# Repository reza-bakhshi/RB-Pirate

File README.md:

<div align="center">

# RB-Pirate

**An RP2350B multi-protocol hardware exploration and debugging tool**

</div>

RB-Pirate is an RP2350B-based tool for communicating with and debugging electronic devices. It combines eight buffered I/O pins, programmable target power, voltage and current monitoring, logic capture, and microSD storage. The terminal interface supports serial-bus interaction and hardware automation.

## Start here

This repository contains the KiCad hardware design. Open [RB-Pirate.kicad_pro](RB-Pirate.kicad_pro) to inspect the schematic and PCB together.

| Resource | Contents |
|---|---|
| [RB-Pirate.kicad_sch](RB-Pirate.kicad_sch) | Schematic entry point |
| [RB-Pirate.kicad_pcb](RB-Pirate.kicad_pcb) | PCB layout |
| [img](img) | Board renders |
| [Custom firmware](https://github.com/reza-bakhshi/RB-Pirate-Firmware) | Build, flashing, terminal operation, and protocol guides |
| [Host automation](https://github.com/reza-bakhshi/RB-Pirate-Skill) | Python serial runner and agent reference material |

Firmware determines which protocol modes and tools are available. RF, infrared, and NFC workflows require the corresponding external hardware; those modules are not built into the base board.

## PCB gallery

<table>
  <tr>
    <th width="50%">Top</th>
    <th width="50%">Bottom</th>
  </tr>
  <tr>
    <td></td>
    <td></td>
  </tr>
</table>

## Hardware features

### RP2350B platform

- Raspberry Pi RP2350B microcontroller
- 128 Mbit program flash
- Dual-core processing and flexible PIO peripherals
- USB-C host connection
- Built-in USB bootloader for straightforward firmware updates
- SWD header, BOOTSEL button, and RESET button
- Two-layer, 1.6 mm PCB designed with KiCad 10

### Eight buffered I/O pins

- 1.65 V to 5 V operating range
- Three-state outputs
- Voltage measurement on every I/O pin
- Individually controllable 10 kΩ pull-up resistors
- Standard 10-pin, 2.54 mm header with GND, BPIO7–BPIO0, and VOUT

### Programmable target power supply

- Programmable 1 V to 5 V output
- Programmable 0 mA to 500 mA current limit
- Real-time current sensing
- Resettable digital fuse
- Output protection circuitry

### Removable microSD storage

- Stores global and protocol-mode settings
- Provides space for logs, captures, dumps, and scripts
- Accessible through the firmware's USB storage interface
- Removable and easy to replace or upgrade

## Software features

### Terminal and logic analysis

- Color VT100 terminal interface
- Live status toolbar with voltage and current monitoring
- Follow-Along Logic Analyzer capture while commands are executed
- Live bus-activity inspection and analysis workflows

### Protocols and workflows

- I²C, SPI, UART, half-duplex UART, 1-Wire, 2-Wire, and 3-Wire communication
- Digital I/O and serial LED control
- JTAG and SWD discovery
- Logic capture and protocol analysis
- EEPROM, flash, FRAM, sensor, and smart-card interaction
- Firmware programming, memory access, scripting, and automation workflows

## Firmware

> [!IMPORTANT]
> ### Use the custom RB-Pirate firmware
>
> Install firmware only from the
> **[RB-Pirate Firmware repository](https://github.com/reza-bakhshi/RB-Pirate-Firmware)**.
> Do not use the mainline Bus Pirate firmware on this board. The custom firmware
> provides the correct hardware configuration, microSD support, and optional
> RGB & Button HAT integration for RB-Pirate.

Build instructions, firmware releases, installation steps, and update
instructions are maintained in the custom firmware repository.

## Optional RGB & Button HAT

The **[RB-Pirate RGB & Button HAT](https://github.com/reza-bakhshi/RB-Pirate-RGB-HAT)**
adds RGB visual feedback and a programmable user button.

The optional HAT provides:

- RGB status indication and animations
- Introduction and party-mode effects
- A button for escaping from active modes
- Scriptable user input for automation and custom workflows

RB-Pirate operates normally without the HAT. Add it only when RGB feedback or
physical button input is useful for your setup.

## License

RB-Pirate is released under the [MIT License](LICENSE).

Third-party components and libraries remain subject to their respective
licenses.

---

<div align="center">
  <sub>Built for hardware exploration, debugging, and experimentation.</sub>
</div>

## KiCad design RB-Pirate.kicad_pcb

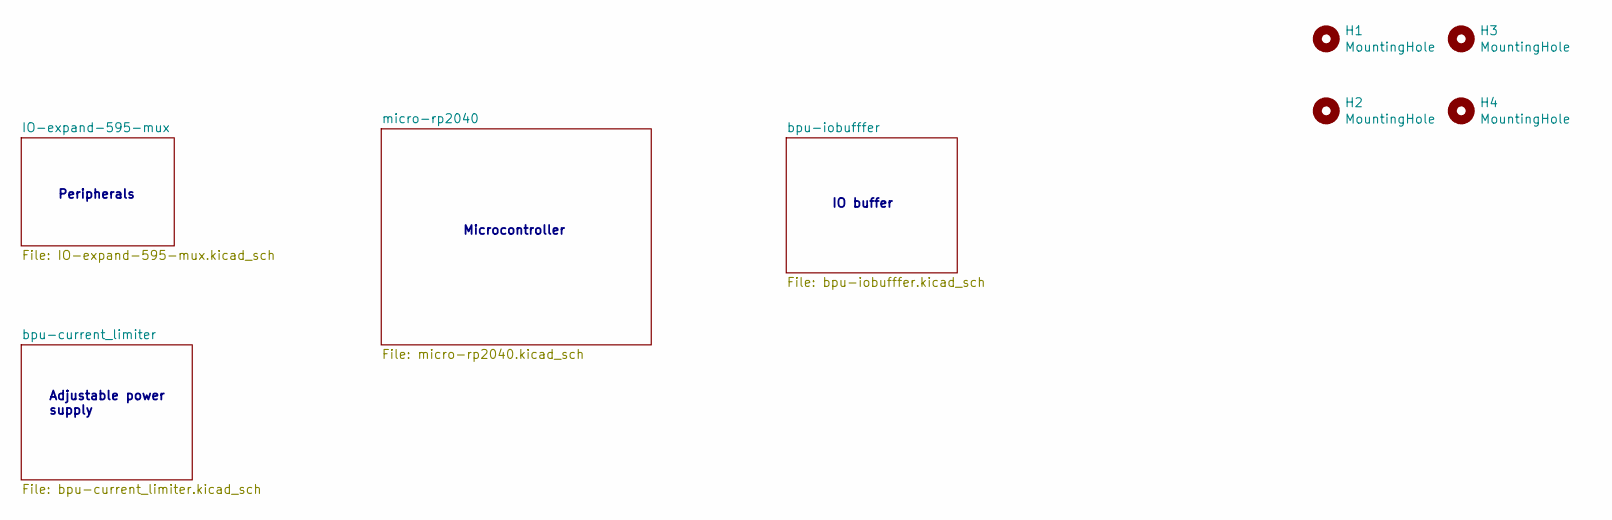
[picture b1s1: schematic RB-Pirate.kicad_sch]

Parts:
H1, H2, H3, H4: MountingHole; MountingHole_3.2mm_M3

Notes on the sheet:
Microcontroller
Adjustable power supply
IO buffer
Peripherals

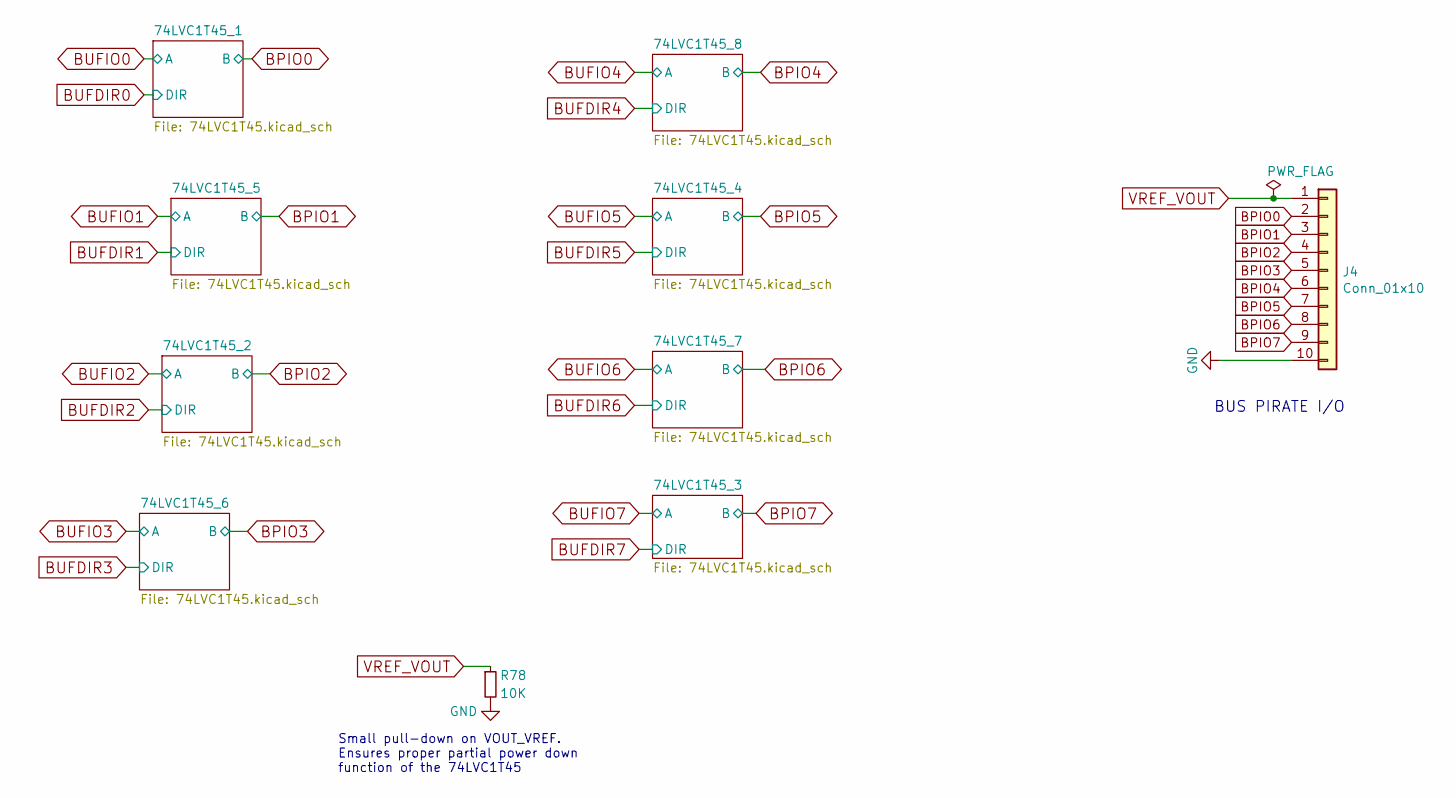
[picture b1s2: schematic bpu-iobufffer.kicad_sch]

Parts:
J4: Conn_01x10; PinHeader_1x10_P2.54mm_Horizontal
R78: 10K; R_0402_1005Metric

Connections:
BPIO0: J4.2; also elsewhere on the board
BPIO1: J4.3; also elsewhere on the board
BPIO2: J4.4; also elsewhere on the board
BPIO3: J4.5; also elsewhere on the board
BPIO4: J4.6; also elsewhere on the board
BPIO5: J4.7; also elsewhere on the board
BPIO6: J4.8; also elsewhere on the board
BPIO7: J4.9; also elsewhere on the board
GND: J4.10, R78.2; also elsewhere on the board
VREF_VOUT: J4.1, R78.1; also elsewhere on the board

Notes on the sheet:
Small pull-down on VOUT_VREF. Ensures proper partial power down function of the 74LVC1T45
BUS PIRATE I/O

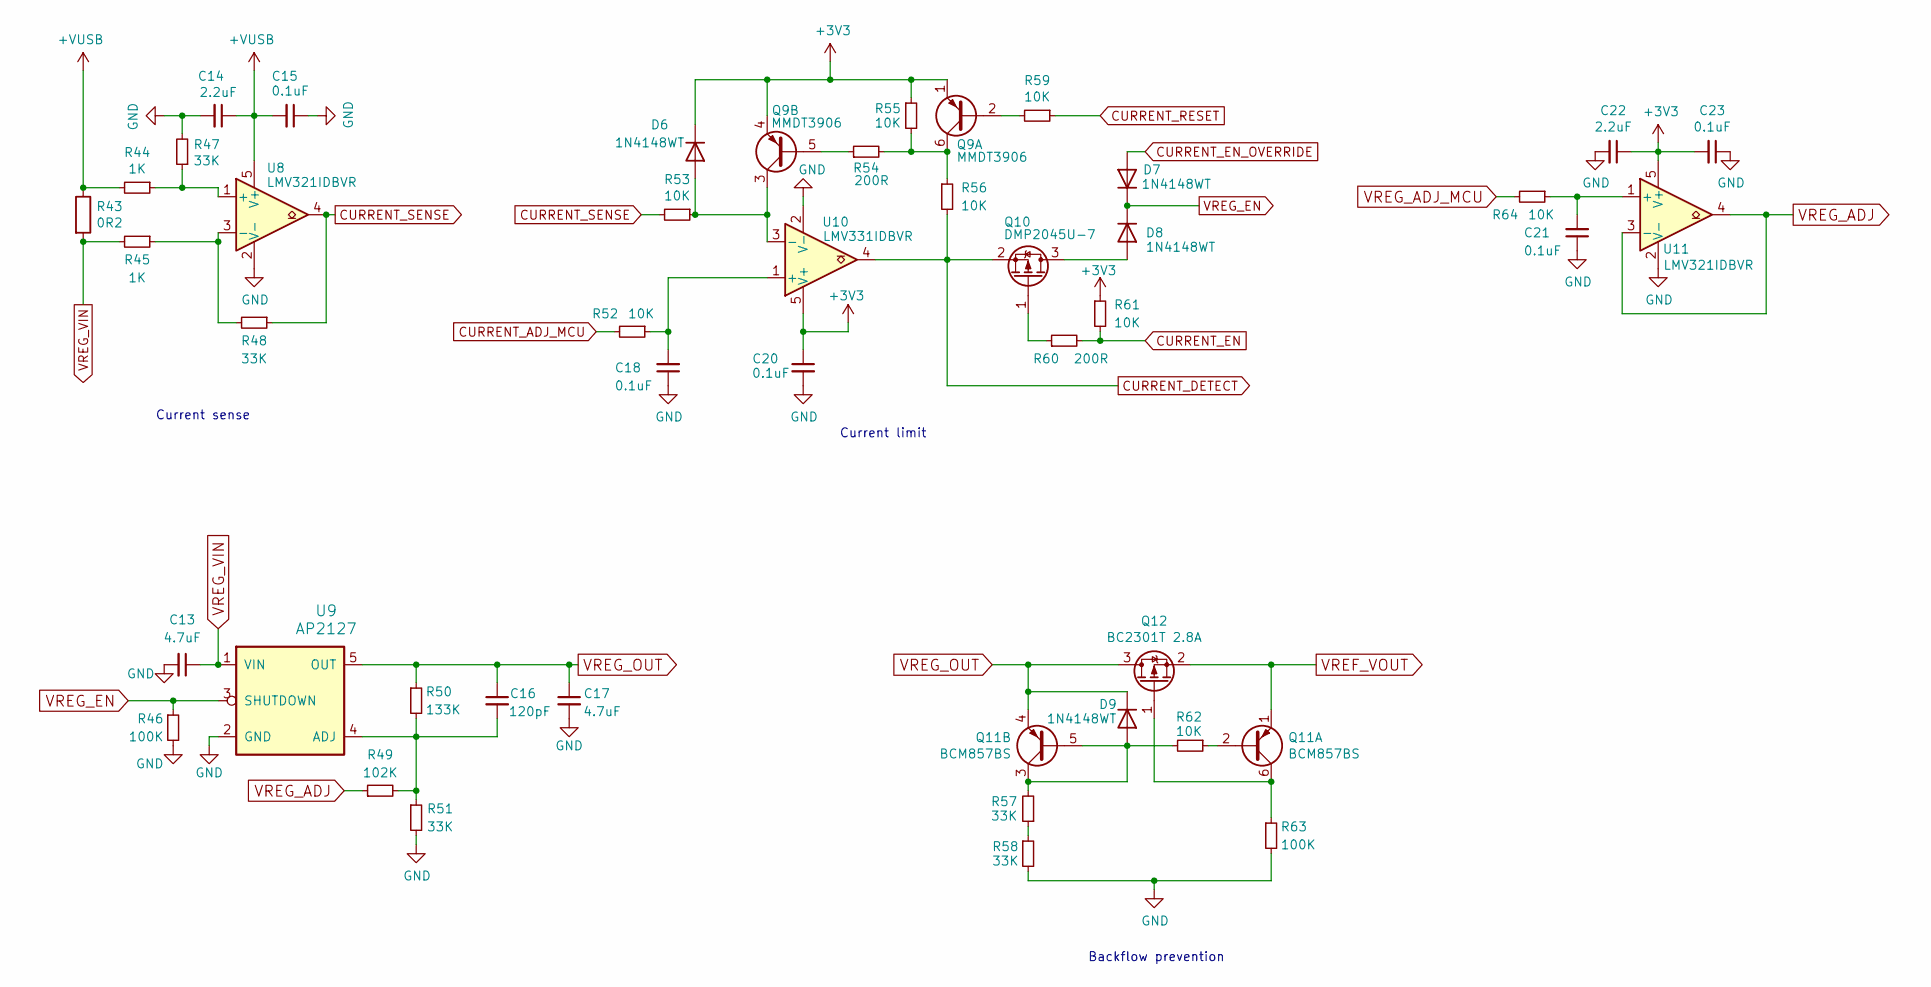
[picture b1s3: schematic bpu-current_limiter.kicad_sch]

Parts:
C13, C17: 4.7uF; C_0402_1005Metric
C14, C22: 2.2uF; C_0402_1005Metric
C15, C18, C20, C21, C23: 0.1uF; C_0402_1005Metric
C16: 120pF; C_0402_1005Metric
D6, D7, D8, D9: 1N4148WT; D_SOD-523
Q9: MMDT3906; SOT-363_SC-70-6
Q10: DMP2045U-7; SOT-23
Q11: BCM857BS; SOT-363_SC-70-6
Q12: BC2301T 2.8A; SOT-23
R43: 0R2; R_2512_6332Metric_Pad1.40x3.35mm_HandSolder
R44, R45: 1K; R_0402_1005Metric
R46, R63: 100K; R_0402_1005Metric
R47, R48, R51, R57, R58: 33K; R_0402_1005Metric
R49: 102K; R_0402_1005Metric
R50: 133K; R_0402_1005Metric
R52, R53, R55, R56, R59, R61, R62, R64: 10K; R_0402_1005Metric
R54, R60: 200R; R_0402_1005Metric
U8, U11: LMV321IDBVR; SOT-23-5
U9: AP2127; SOT-23-5
U10: LMV331IDBVR; SOT-23-5

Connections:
+3V3: C20.1, C22.1, C23.2, D6.1 (K), Q9.1 (E1), Q9.4 (E2), R55.1, R61.1, U10.5 (V+), U11.5 (V+); also elsewhere on the board
+VUSB: C14.1, C15.2, R43.1, R44.2, U8.5 (V+); also elsewhere on the board
CURRENT_ADJ_MCU: R52.2; also elsewhere on the board
CURRENT_DETECT: Q10.2 (S), R56.2, U10.4; also elsewhere on the board
CURRENT_EN: R60.2, R61.2; also elsewhere on the board
CURRENT_EN_OVERRIDE: D7.2 (A); also elsewhere on the board
CURRENT_RESET: R59.1; also elsewhere on the board
CURRENT_SENSE: R48.1, R53.2, U8.4; also elsewhere on the board
GND: C13.2, C14.2, C15.1, C17.2, C18.1, C20.2, C21.1, C22.2, C23.1, R46.2, R47.2, R51.2, R58.2, R63.2, U8.2 (V-), U9.2 (GND), U10.2 (V-), U11.2 (V-); also elsewhere on the board
unnamed: D6.2 (A), Q9.3 (C2), R53.1, U10.3 (-)
unnamed: D8.2 (A), Q10.3 (D)
unnamed: D9.2 (A), Q11.3 (C2), Q11.5 (B2), R57.2, R62.2
unnamed: Q9.2 (B1), R59.2
unnamed: Q9.6 (C1), R54.2, R55.2, R56.1
unnamed: Q9.5 (B2), R54.1
unnamed: Q10.1 (G), R60.1
unnamed: Q11.2 (B1), R62.1
unnamed: Q11.6 (C1), Q12.1 (G), R63.1
unnamed: R57.1, R58.1
unnamed: R44.1, R47.1, U8.1 (+)
unnamed: R45.1, R48.2, U8.3 (-)
unnamed: C16.2, R49.2, R50.2, R51.1, U9.4 (ADJ)
unnamed: C18.2, R52.1, U10.1 (+)
unnamed: C21.2, R64.1, U11.1 (+)
VREF_VOUT: Q11.1 (E1), Q12.2 (S); also elsewhere on the board
VREG_ADJ: R49.1, U11.3 (-), U11.4
VREG_ADJ_MCU: R64.2; also elsewhere on the board
VREG_EN: D7.1 (K), D8.1 (K), R46.1, U9.3 (SHUTDOWN)
VREG_OUT: C16.1, C17.1, D9.1 (K), Q11.4 (E2), Q12.3 (D), R50.1, U9.5 (OUT); also elsewhere on the board
VREG_VIN: C13.1, R43.2, R45.2, U9.1 (VIN)

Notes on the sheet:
Current sense
Backflow prevention
Current limit

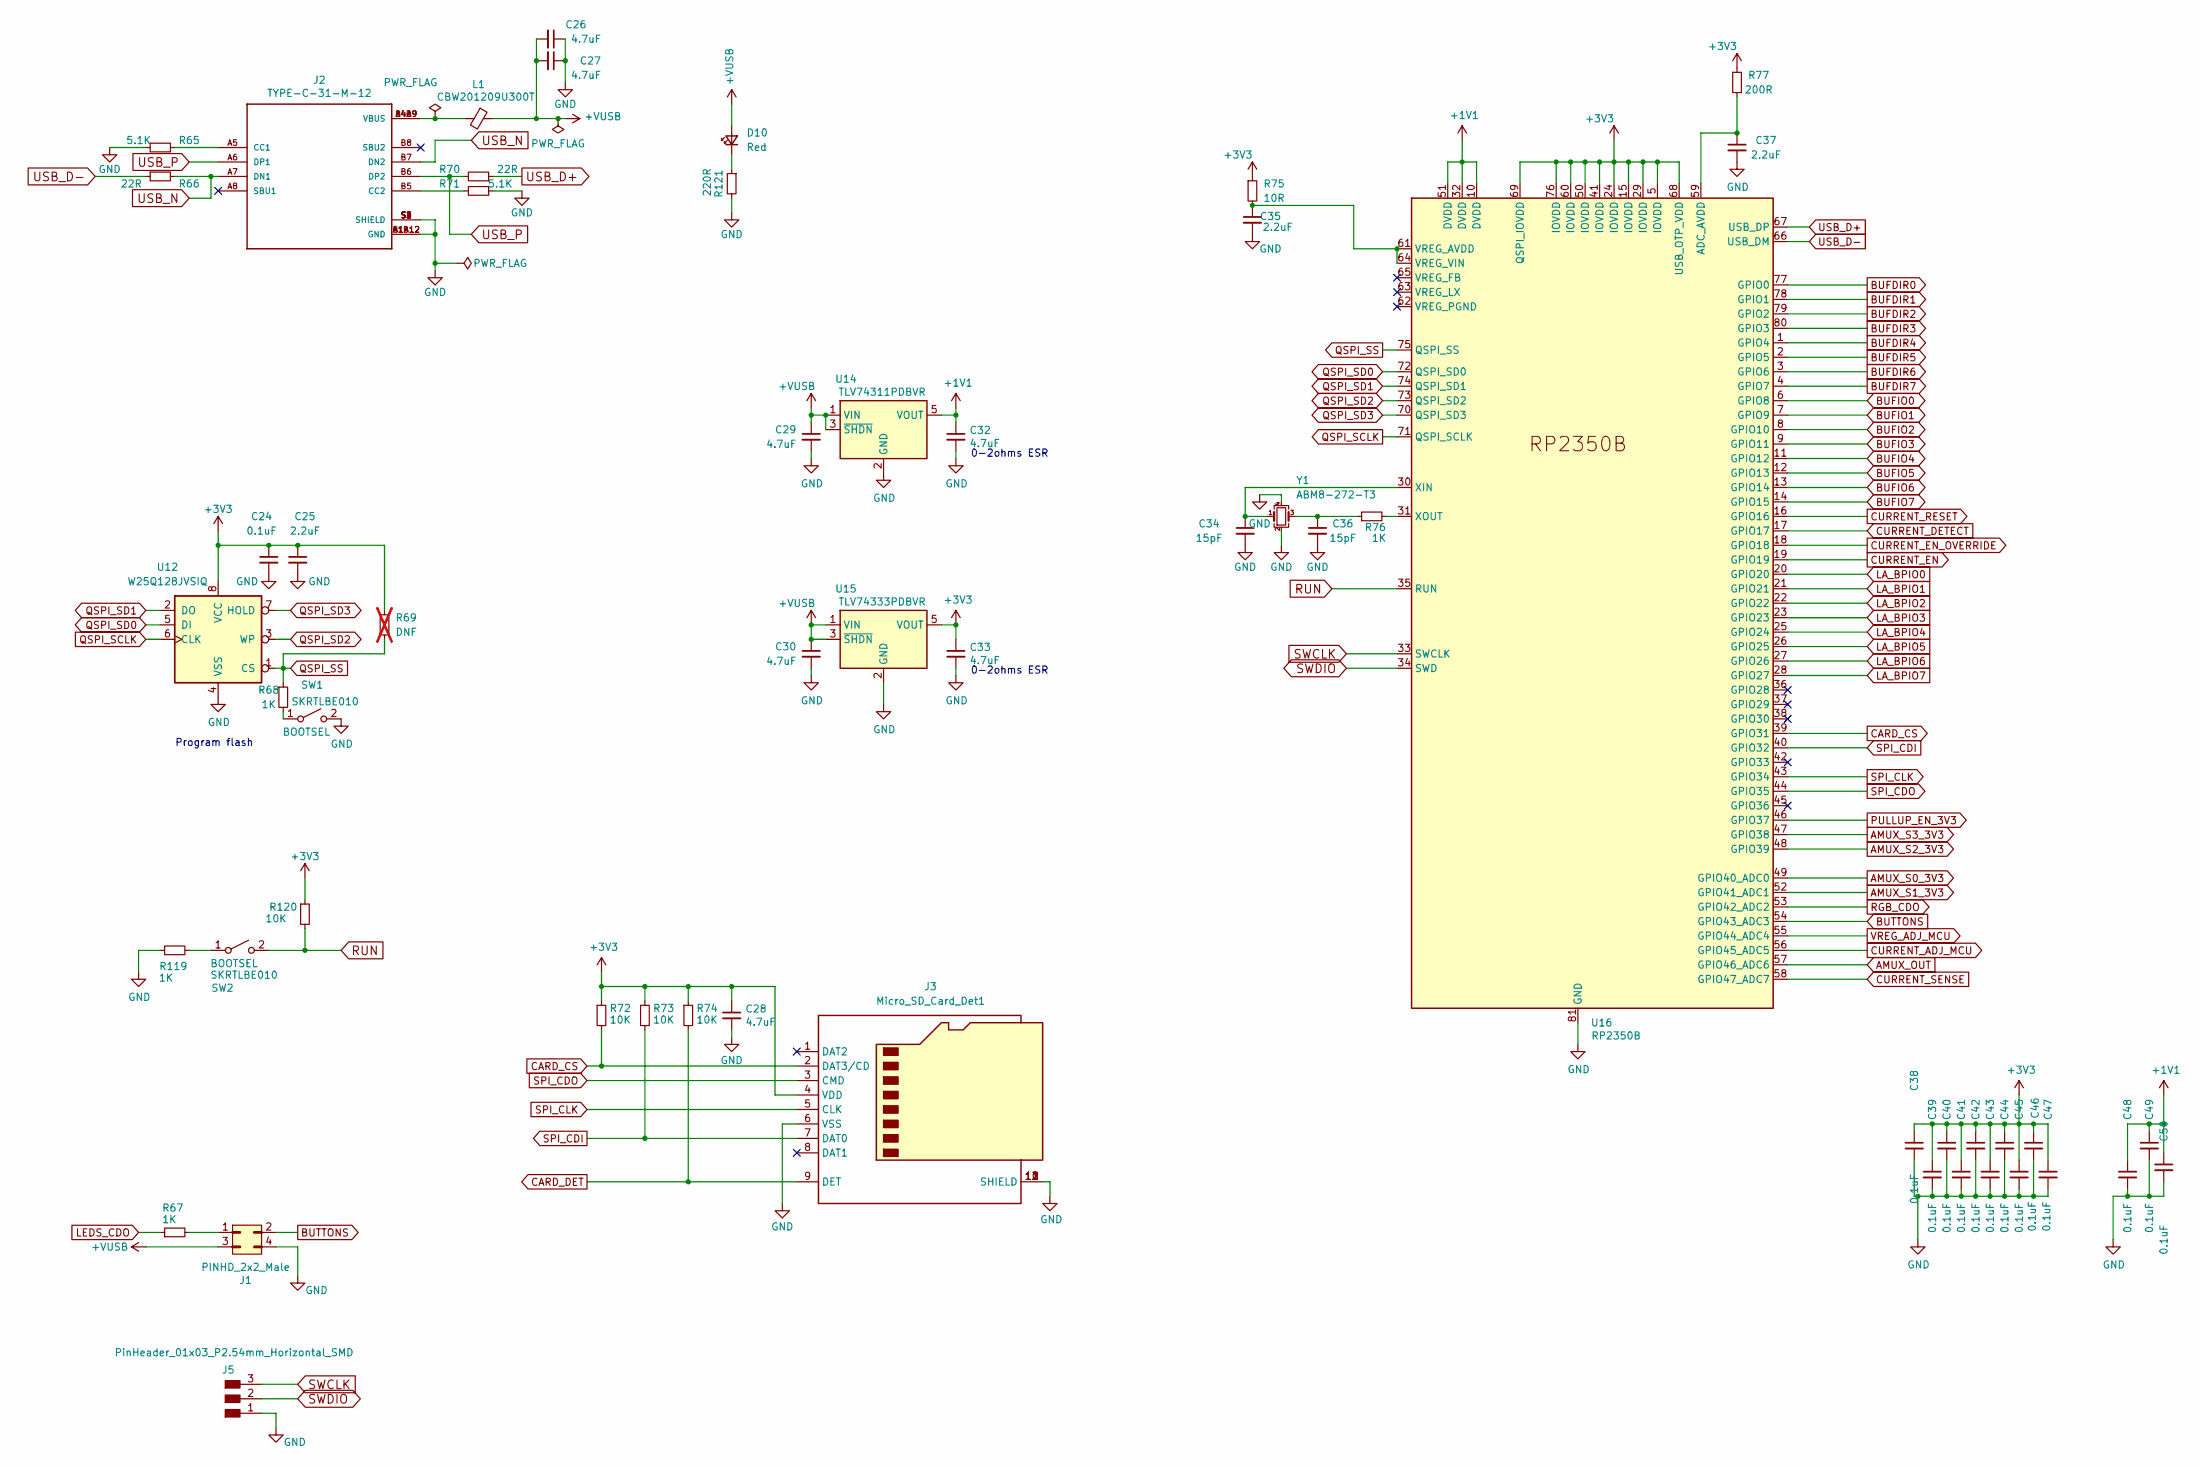
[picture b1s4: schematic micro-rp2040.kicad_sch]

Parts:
C24, C38, C39, C40, C41, C42, C43, C44, C45, C46, C47, C48, C49, C50: 0.1uF; C_0402_1005Metric
C25, C35, C37: 2.2uF; C_0402_1005Metric
C26, C27, C28, C29, C30, C32, C33: 4.7uF; C_0402_1005Metric
C34, C36: 15pF; C_0402_1005Metric
D10: Red; LED_0402_1005Metric_Red
J1: PINHD_2x2_Male; PinHeader_2x02_P2.54mm_Vertical_SMD
J2: TYPE-C-31-M-12; HRO_TYPE-C-31-M-12
J3: Micro_SD_Card_Det1; microSD_External_Pin
J5: PinHeader_01x03_P2.54mm_Horizontal_SMD
L1: CBW201209U300T; L_0805_2012Metric
R65, R71: 5.1K; R_0402_1005Metric
R66, R70: 22R; R_0402_1005Metric
R67, R68, R76, R119: 1K; R_0402_1005Metric
R69: DNF; R_0402_1005Metric; not fitted
R72, R73, R74, R120: 10K; R_0402_1005Metric
R75: 10R; R_0402_1005Metric
R77: 200R; R_0402_1005Metric
R121: 220R; R_0402_1005Metric
SW1, SW2: SKRTLBE010; Push_SMD_RA_4.5x3.4mm
U12: W25Q128JVSIQ; SOP-8_5.28x5.23mm_P1.27mm
U14: TLV74311PDBVR; SOT-23-5
U15: TLV74333PDBVR; SOT-23-5
U16: RP2350B; qfn80
Y1: ABM8-272-T3; Crystal_SMD_4Pin

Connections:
+1V1: C32.1, C48.1, C49.1, C50.1, U14.5 (VOUT), U16.10 (DVDD), U16.32 (DVDD), U16.51 (DVDD)
+3V3: C24.1, C25.1, C28.1, C33.1, C38.1, C39.1, C40.1, C41.1, C42.1, C43.1, C44.1, C45.1, C46.1, C47.1, J3.4 (VDD), R69.1, R72.1, R73.1, R74.1, R75.1, R77.1, R120.1, U12.8 (VCC), U15.5 (VOUT), U16.5 (IOVDD), U16.15 (IOVDD), U16.24 (IOVDD), U16.29 (IOVDD), U16.41 (IOVDD), U16.50 (IOVDD), U16.60 (IOVDD), U16.68 (USB_OTP_VDD), U16.69 (QSPI_IOVDD), U16.76 (IOVDD); also elsewhere on the board
+VUSB: C26.2, C27.2, C29.1, C30.1, D10.2 (A), J1.3, L1.1, U14.1 (VIN), U14.3 (~SHDN), U15.1 (VIN), U15.3 (~SHDN); also elsewhere on the board
AMUX_OUT: U16.57 (GPIO46_ADC6); also elsewhere on the board
AMUX_S0_3V3: U16.49 (GPIO40_ADC0); also elsewhere on the board
AMUX_S1_3V3: U16.52 (GPIO41_ADC1); also elsewhere on the board
AMUX_S2_3V3: U16.48 (GPIO39); also elsewhere on the board
AMUX_S3_3V3: U16.47 (GPIO38); also elsewhere on the board
BUFDIR0: U16.77 (GPIO0); also elsewhere on the board
BUFDIR1: U16.78 (GPIO1); also elsewhere on the board
BUFDIR2: U16.79 (GPIO2); also elsewhere on the board
BUFDIR3: U16.80 (GPIO3); also elsewhere on the board
BUFDIR4: U16.1 (GPIO4); also elsewhere on the board
BUFDIR5: U16.2 (GPIO5); also elsewhere on the board
BUFDIR6: U16.3 (GPIO6); also elsewhere on the board
BUFDIR7: U16.4 (GPIO7); also elsewhere on the board
BUFIO0: U16.6 (GPIO8); also elsewhere on the board
BUFIO1: U16.7 (GPIO9); also elsewhere on the board
BUFIO2: U16.8 (GPIO10); also elsewhere on the board
BUFIO3: U16.9 (GPIO11); also elsewhere on the board
BUFIO4: U16.11 (GPIO12); also elsewhere on the board
BUFIO5: U16.12 (GPIO13); also elsewhere on the board
BUFIO6: U16.13 (GPIO14); also elsewhere on the board
BUFIO7: U16.14 (GPIO15); also elsewhere on the board
BUTTONS: J1.2, U16.54 (GPIO43_ADC3)
CARD_CS: J3.2 (DAT3/CD), R72.2, U16.39 (GPIO31)
CARD_DET: J3.9 (DET), R74.2; also elsewhere on the board
CURRENT_ADJ_MCU: U16.56 (GPIO45_ADC5); also elsewhere on the board
CURRENT_DETECT: U16.17 (GPIO17); also elsewhere on the board
CURRENT_EN: U16.19 (GPIO19); also elsewhere on the board
CURRENT_EN_OVERRIDE: U16.18 (GPIO18); also elsewhere on the board
CURRENT_RESET: U16.16 (GPIO16); also elsewhere on the board
CURRENT_SENSE: U16.58 (GPIO47_ADC7); also elsewhere on the board
GND: C24.2, C25.2, C26.1, C27.1, C28.2, C29.2, C30.2, C32.2, C33.2, C34.2, C35.2, C36.2, C37.2, C38.2, C39.2, C40.2, C41.2, C42.2, C43.2, C44.2, C45.2, C46.2, C47.2, C48.2, C49.2, C50.2, J1.4, J2.A1B12 (GND), J2.B1A12 (GND), J2.S1 (SHIELD), J2.S2 (SHIELD), J2.S3 (SHIELD), J2.S4 (SHIELD), J3.6 (VSS), J3.10 (SHIELD), J3.11 (SHIELD), J3.12 (SHIELD), J3.13 (SHIELD), J5.1, R65.1, R71.1, R119.1, R121.2, SW1.2 (B), U12.4 (VSS), U14.2 (GND), U14.4 (GND), U15.2 (GND), U15.4 (GND), U16.81 (GND), Y1.2, Y1.4; also elsewhere on the board
LA_BPIO0: U16.20 (GPIO20); also elsewhere on the board
LA_BPIO1: U16.21 (GPIO21); also elsewhere on the board
LA_BPIO2: U16.22 (GPIO22); also elsewhere on the board
LA_BPIO3: U16.23 (GPIO23); also elsewhere on the board
LA_BPIO4: U16.25 (GPIO24); also elsewhere on the board
LA_BPIO5: U16.26 (GPIO25); also elsewhere on the board
LA_BPIO6: U16.27 (GPIO26); also elsewhere on the board
LA_BPIO7: U16.28 (GPIO27); also elsewhere on the board
LEDS_CDO: R67.1; also elsewhere on the board
unnamed: C36.1, R76.1, Y1.3
unnamed: D10.1 (K), R121.1
unnamed: J1.1, R67.2
unnamed: J2.A5 (CC1), R65.2
unnamed: J2.B5 (CC2), R71.2
unnamed: J2.A4B9 (VBUS), J2.B4A9 (VBUS), L1.2
unnamed: R68.2, SW1.1 (A)
unnamed: R119.2, SW2.1 (A)
unnamed: C37.1, R77.2, U16.59 (ADC_AVDD)
unnamed: C35.1, R75.2, U16.61 (VREG_AVDD), U16.64 (VREG_VIN)
unnamed: C34.1, U16.30 (XIN), Y1.1
unnamed: R76.2, U16.31 (XOUT)
PULLUP_EN_3V3: U16.46 (GPIO37); also elsewhere on the board
QSPI_SCLK: U12.6 (CLK), U16.71 (QSPI_SCLK)
QSPI_SD0: U12.5 (DI), U16.72 (QSPI_SD0)
QSPI_SD1: U12.2 (DO), U16.74 (QSPI_SD1)
QSPI_SD2: U12.3 (WP), U16.73 (QSPI_SD2)
QSPI_SD3: U12.7 (HOLD), U16.70 (QSPI_SD3)
QSPI_SS: R68.1, R69.2, U12.1 (CS), U16.75 (QSPI_SS)
RGB_CDO: U16.53 (GPIO42_ADC2); also elsewhere on the board
RUN: R120.2, SW2.2 (B), U16.35 (RUN)
SPI_CDI: J3.7 (DAT0), R73.2, U16.40 (GPIO32)
SPI_CDO: J3.3 (CMD), U16.44 (GPIO35)
SPI_CLK: J3.5 (CLK), U16.43 (GPIO34)
SWCLK: J5.3, U16.33 (SWCLK)
SWDIO: J5.2, U16.34 (SWD)
USB_D+: R70.1, U16.67 (USB_DP)
USB_D-: R66.1, U16.66 (USB_DM)
USB_N: J2.A7 (DN1), J2.B7 (DN2), R66.2
USB_P: J2.A6 (DP1), J2.B6 (DP2), R70.2
VREG_ADJ_MCU: U16.55 (GPIO44_ADC4); also elsewhere on the board

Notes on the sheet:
Program flash
0-2ohms ESR

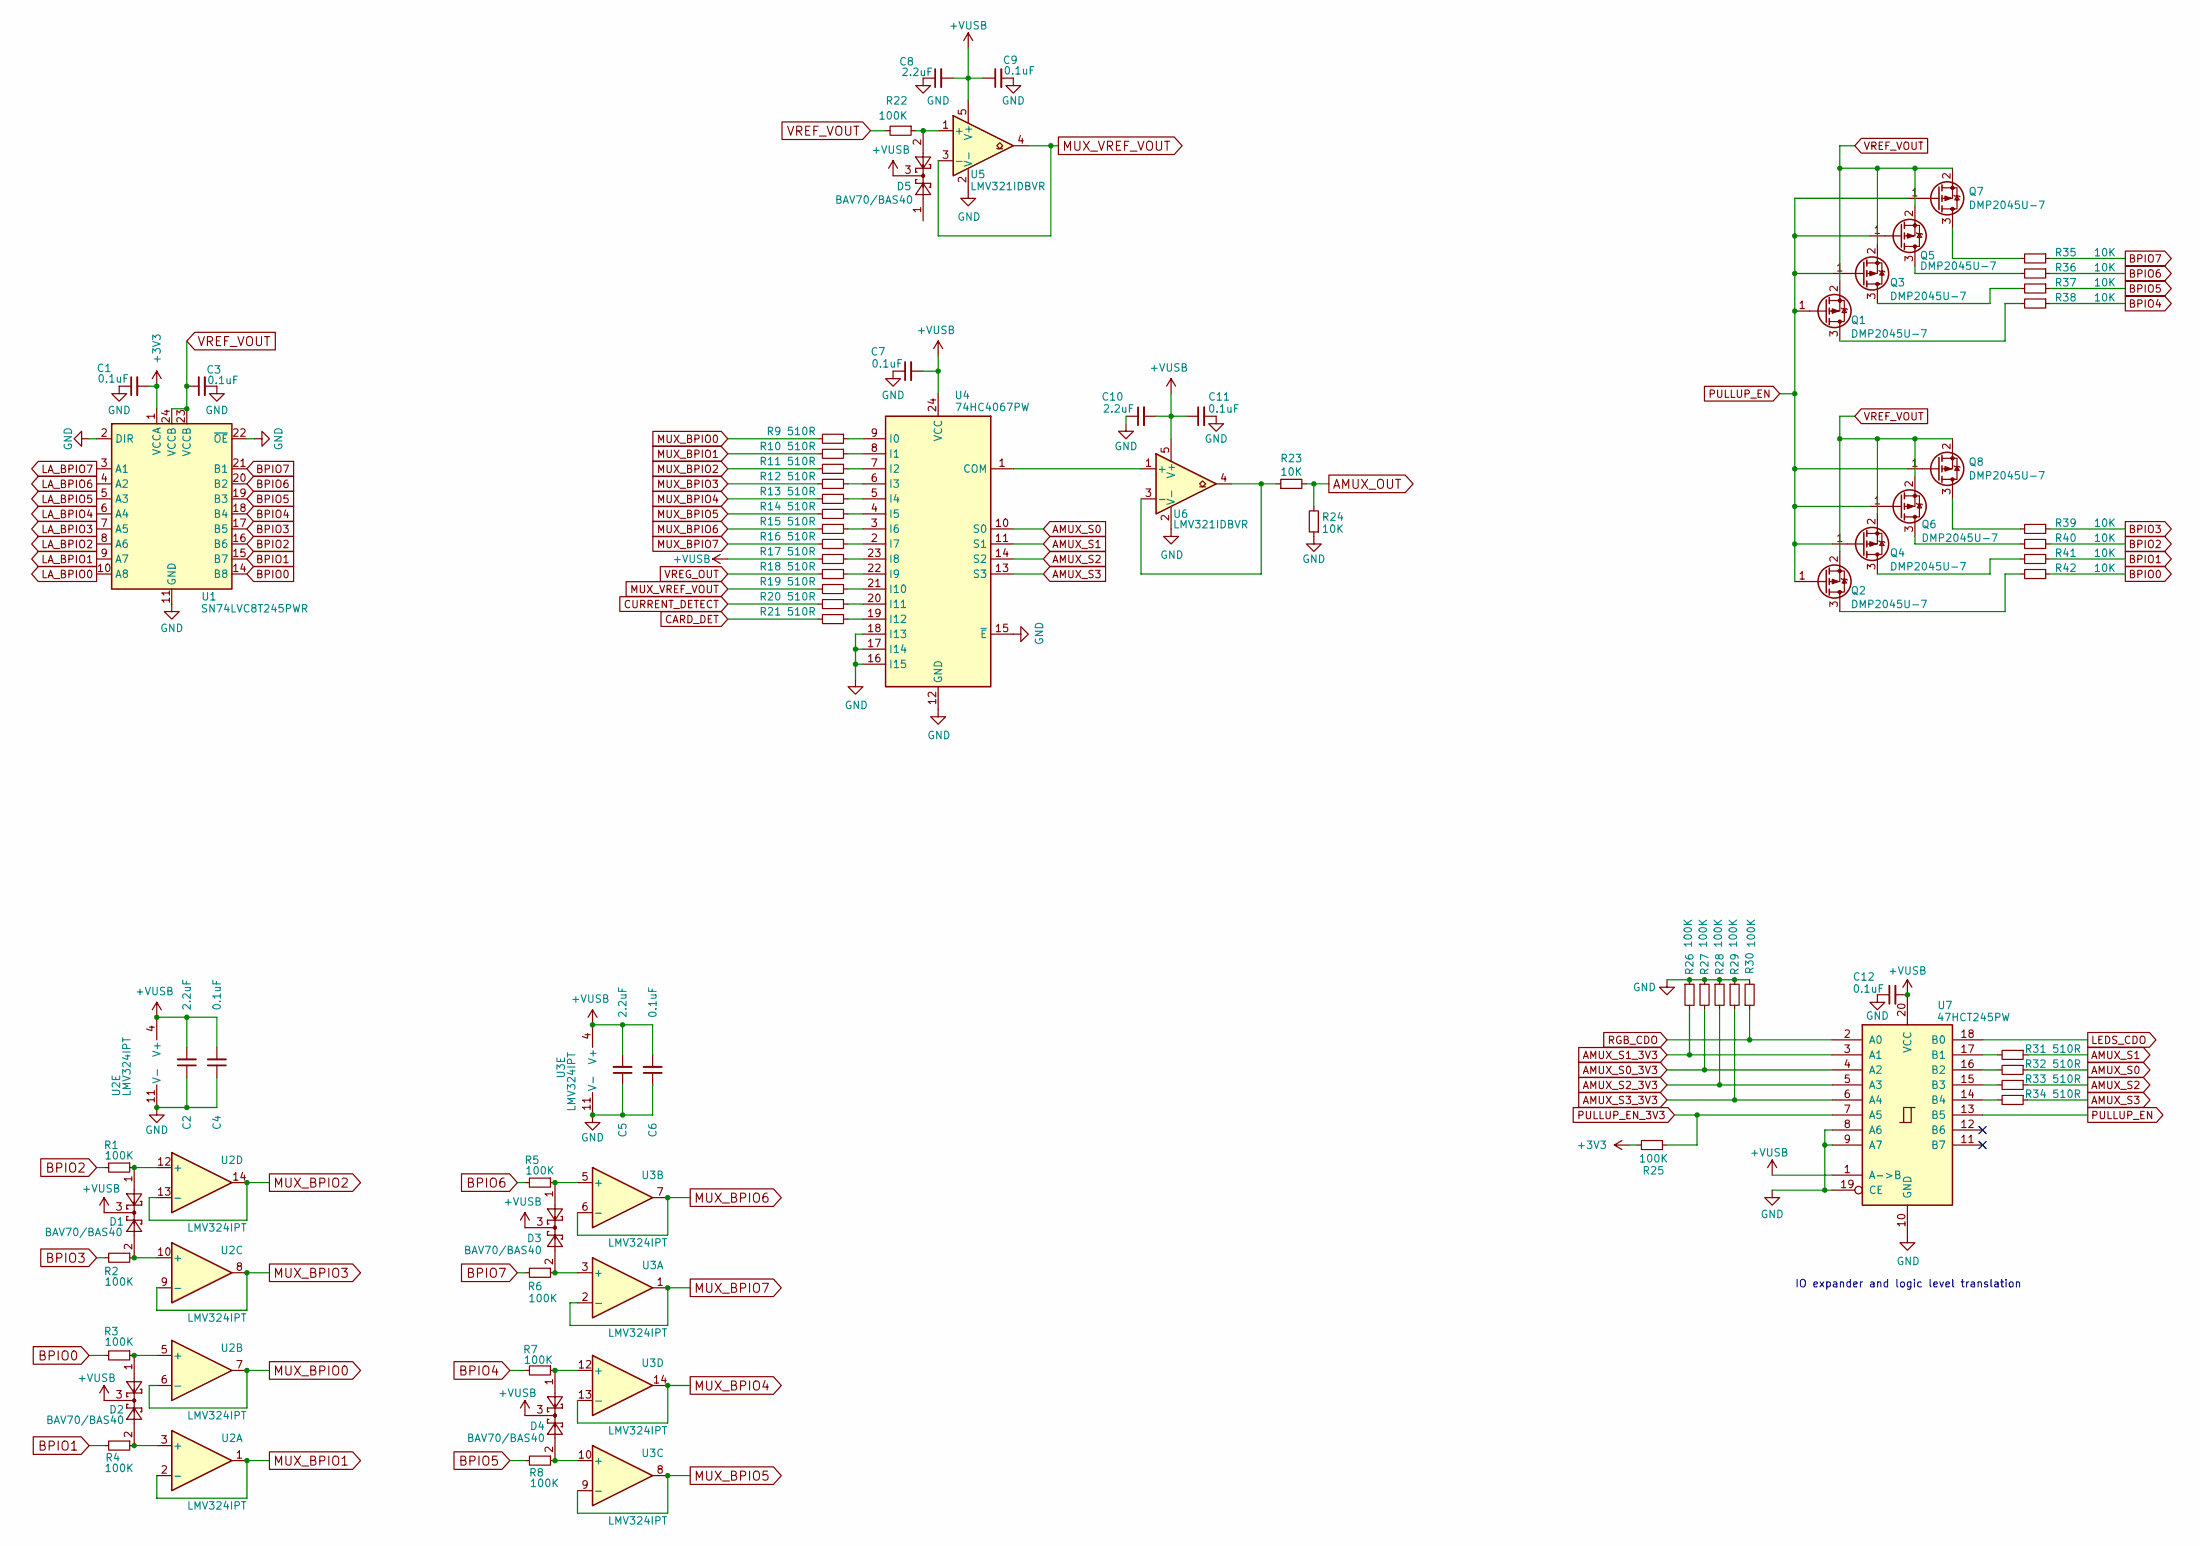
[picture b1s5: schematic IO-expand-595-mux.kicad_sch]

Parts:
C1, C3, C4, C6, C7, C9, C11, C12: 0.1uF; C_0402_1005Metric
C2, C5, C8, C10: 2.2uF; C_0402_1005Metric
D1, D2, D3, D4, D5: BAV70/BAS40; SOT-23
Q1, Q2, Q3, Q4, Q5, Q6, Q7, Q8: DMP2045U-7; SOT-23
R1, R2, R3, R4, R5, R6, R7, R8, R22, R25, R26, R27, R28, R29, R30: 100K; R_0402_1005Metric
R9, R10, R11, R12, R13, R14, R15, R16, R17, R18, R19, R20, R21, R31, R32, R33, R34: 510R; R_0402_1005Metric
R23, R24, R35, R36, R37, R38, R39, R40, R41, R42: 10K; R_0402_1005Metric
U1: SN74LVC8T245PWR; TSSOP-24_4.4x7.8mm_P0.65mm
U2, U3: LMV324IPT; TSSOP-14_4.4x5mm_P0.65mm
U4: 74HC4067PW; TSSOP-24_4.4x7.8mm_P0.65mm
U5, U6: LMV321IDBVR; SOT-23-5
U7: 47HCT245PW; TSSOP-20_4.4x6.5mm_P0.65mm

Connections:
+3V3: C1.2, R25.2, U1.1 (VCCA); also elsewhere on the board
+VUSB: C2.2, C4.2, C5.2, C6.2, C7.2, C8.2, C9.1, C10.2, C11.1, C12.2, D1.3, D2.3, D3.3, D4.3, D5.3, R17.2, U2.4 (V+), U3.4 (V+), U4.24 (VCC), U5.5 (V+), U6.5 (V+), U7.1 (A->B), U7.20 (VCC); also elsewhere on the board
AMUX_OUT: R23.2, R24.2; also elsewhere on the board
AMUX_S0: R32.1, U4.10 (S0)
AMUX_S0_3V3: R27.2, U7.4 (A2); also elsewhere on the board
AMUX_S1: R31.1, U4.11 (S1)
AMUX_S1_3V3: R26.2, U7.3 (A1); also elsewhere on the board
AMUX_S2: R33.1, U4.14 (S2)
AMUX_S2_3V3: R28.2, U7.5 (A3); also elsewhere on the board
AMUX_S3: R34.1, U4.13 (S3)
AMUX_S3_3V3: R29.2, U7.6 (A4); also elsewhere on the board
BPIO0: R3.2, R42.1, U1.14 (B8); also elsewhere on the board
BPIO1: R4.2, R41.1, U1.15 (B7); also elsewhere on the board
BPIO2: R1.2, R40.1, U1.16 (B6); also elsewhere on the board
BPIO3: R2.2, R39.1, U1.17 (B5); also elsewhere on the board
BPIO4: R7.2, R38.1, U1.18 (B4); also elsewhere on the board
BPIO5: R8.2, R37.1, U1.19 (B3); also elsewhere on the board
BPIO6: R5.2, R36.1, U1.20 (B2); also elsewhere on the board
BPIO7: R6.2, R35.1, U1.21 (B1); also elsewhere on the board
CARD_DET: R21.2; also elsewhere on the board
CURRENT_DETECT: R20.2; also elsewhere on the board
GND: C1.1, C2.1, C3.2, C4.1, C5.1, C6.1, C7.1, C8.1, C9.2, C10.1, C11.2, C12.1, R24.1, R26.1, R27.1, R28.1, R29.1, R30.2, U1.2 (DIR), U1.11 (GND), U1.12 (GND), U1.13 (GND), U1.22 (~OE), U2.11 (V-), U3.11 (V-), U4.12 (GND), U4.15 (~E), U4.16 (I15), U4.17 (I14), U4.18 (I13), U5.2 (V-), U6.2 (V-), U7.8 (A6), U7.9 (A7), U7.10 (GND), U7.19 (CE); also elsewhere on the board
LA_BPIO0: U1.10 (A8); also elsewhere on the board
LA_BPIO1: U1.9 (A7); also elsewhere on the board
LA_BPIO2: U1.8 (A6); also elsewhere on the board
LA_BPIO3: U1.7 (A5); also elsewhere on the board
LA_BPIO4: U1.6 (A4); also elsewhere on the board
LA_BPIO5: U1.5 (A3); also elsewhere on the board
LA_BPIO6: U1.4 (A2); also elsewhere on the board
LA_BPIO7: U1.3 (A1); also elsewhere on the board
LEDS_CDO: U7.18 (B0); also elsewhere on the board
MUX_BPIO0: R9.2, U2.6 (-), U2.7
MUX_BPIO1: R10.2, U2.1, U2.2 (-)
MUX_BPIO2: R11.2, U2.13 (-), U2.14
MUX_BPIO3: R12.2, U2.8, U2.9 (-)
MUX_BPIO4: R13.2, U3.13 (-), U3.14
MUX_BPIO5: R14.2, U3.8, U3.9 (-)
MUX_BPIO6: R15.2, U3.6 (-), U3.7
MUX_BPIO7: R16.2, U3.1, U3.2 (-)
MUX_VREF_VOUT: R19.2, U5.3 (-), U5.4
unnamed: Q1.3 (D), R38.2
unnamed: Q2.3 (D), R42.2
unnamed: Q3.3 (D), R37.2
unnamed: Q4.3 (D), R41.2
unnamed: Q5.3 (D), R36.2
unnamed: Q6.3 (D), R40.2
unnamed: Q7.3 (D), R35.2
unnamed: Q8.3 (D), R39.2
unnamed: D2.2, R4.1, U2.3 (+)
unnamed: D2.1, R3.1, U2.5 (+)
unnamed: D1.2, R2.1, U2.10 (+)
unnamed: D1.1, R1.1, U2.12 (+)
unnamed: D3.2, R6.1, U3.3 (+)
unnamed: D3.1, R5.1, U3.5 (+)
unnamed: D4.2, R8.1, U3.10 (+)
unnamed: D4.1, R7.1, U3.12 (+)
unnamed: U4.1 (COM), U6.1 (+)
unnamed: R9.1, U4.9 (I0)
unnamed: R10.1, U4.8 (I1)
unnamed: R11.1, U4.7 (I2)
unnamed: R12.1, U4.6 (I3)
unnamed: R13.1, U4.5 (I4)
unnamed: R14.1, U4.4 (I5)
unnamed: R15.1, U4.3 (I6)
unnamed: R16.1, U4.2 (I7)
unnamed: R17.1, U4.23 (I8)
unnamed: R18.1, U4.22 (I9)
unnamed: R19.1, U4.21 (I10)
unnamed: R20.1, U4.20 (I11)
unnamed: R21.1, U4.19 (I12)
unnamed: D5.2, R22.1, U5.1 (+)
unnamed: R23.1, U6.3 (-), U6.4
unnamed: R31.2, U7.17 (B1)
unnamed: R32.2, U7.16 (B2)
unnamed: R33.2, U7.15 (B3)
unnamed: R34.2, U7.14 (B4)
PULLUP_EN: Q1.1 (G), Q2.1 (G), Q3.1 (G), Q4.1 (G), Q5.1 (G), Q6.1 (G), Q7.1 (G), Q8.1 (G), U7.13 (B5)
PULLUP_EN_3V3: R25.1, U7.7 (A5); also elsewhere on the board
RGB_CDO: R30.1, U7.2 (A0); also elsewhere on the board
VREF_VOUT: C3.1, Q1.2 (S), Q2.2 (S), Q3.2 (S), Q4.2 (S), Q5.2 (S), Q6.2 (S), Q7.2 (S), Q8.2 (S), R22.2, U1.23 (VCCB), U1.24 (VCCB); also elsewhere on the board
VREG_OUT: R18.2; also elsewhere on the board

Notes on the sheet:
IO expander and logic level translation

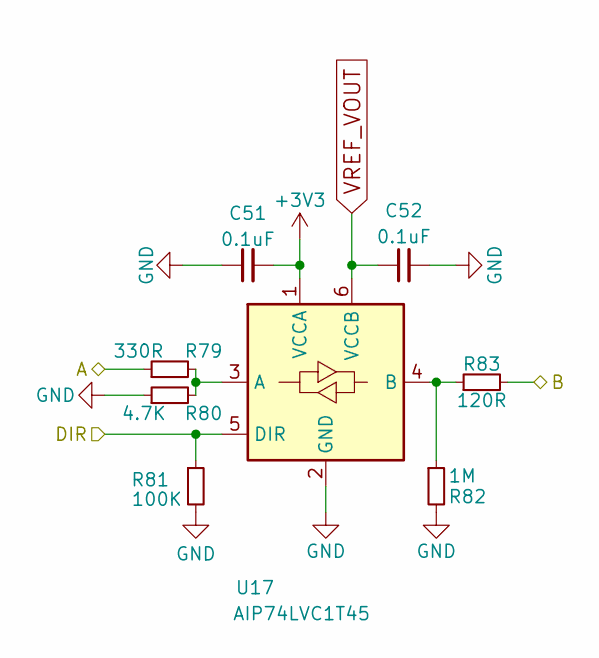
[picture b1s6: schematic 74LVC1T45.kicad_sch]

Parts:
C51, C52: 0.1uF; C_0402_1005Metric
R79: 330R; R_0402_1005Metric
R80: 4.7K; R_0402_1005Metric
R81: 100K; R_0402_1005Metric
R82: 1M; R_0402_1005Metric
R83: 120R; R_0402_1005Metric
U17: AIP74LVC1T45; SOT-363_SC-70-6

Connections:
+3V3: C51.2, U17.1 (VCCA); also elsewhere on the board
BPIO0: R83.2; also elsewhere on the board
BUFDIR0: R81.1, U17.5 (DIR); also elsewhere on the board
BUFIO0: R79.1; also elsewhere on the board
GND: C51.1, C52.2, R80.1, R81.2, R82.2, U17.2 (GND); also elsewhere on the board
unnamed: R79.2, R80.2, U17.3 (A)
unnamed: R82.1, R83.1, U17.4 (B)
VREF_VOUT: C52.1, U17.6 (VCCB); also elsewhere on the board

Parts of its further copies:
C53, C54, C55, C56, C57, C58, C59, C60, C61, C62, C63, C64, C65, C66: 0.1uF; C_0402_1005Metric
R84, R89, R94, R99, R104, R109, R114: 330R; R_0402_1005Metric
R85, R90, R95, R100, R105, R110, R115: 4.7K; R_0402_1005Metric
R86, R91, R96, R101, R106, R111, R116: 100K; R_0402_1005Metric
R87, R92, R97, R102, R107, R112, R117: 1M; R_0402_1005Metric
R88, R93, R98, R103, R108, R113, R118: 120R; R_0402_1005Metric
U18, U19, U20, U21, U22, U23, U24: AIP74LVC1T45; SOT-363_SC-70-6

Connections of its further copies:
+3V3: C53.2, C55.2, C57.2, C59.2, C61.2, C63.2, C65.2, U18.1 (VCCA), U19.1 (VCCA), U20.1 (VCCA), U21.1 (VCCA), U22.1 (VCCA), U23.1 (VCCA), U24.1 (VCCA); also elsewhere on the board
BPIO1: R103.2; also elsewhere on the board
BPIO2: R88.2; also elsewhere on the board
BPIO3: R108.2; also elsewhere on the board
BPIO4: R118.2; also elsewhere on the board
BPIO5: R98.2; also elsewhere on the board
BPIO6: R113.2; also elsewhere on the board
BPIO7: R93.2; also elsewhere on the board
BUFDIR1: R101.1, U21.5 (DIR); also elsewhere on the board
BUFDIR2: R86.1, U18.5 (DIR); also elsewhere on the board
BUFDIR3: R106.1, U22.5 (DIR); also elsewhere on the board
BUFDIR4: R116.1, U24.5 (DIR); also elsewhere on the board
BUFDIR5: R96.1, U20.5 (DIR); also elsewhere on the board
BUFDIR6: R111.1, U23.5 (DIR); also elsewhere on the board
BUFDIR7: R91.1, U19.5 (DIR); also elsewhere on the board
BUFIO1: R99.1; also elsewhere on the board
BUFIO2: R84.1; also elsewhere on the board
BUFIO3: R104.1; also elsewhere on the board
BUFIO4: R114.1; also elsewhere on the board
BUFIO5: R94.1; also elsewhere on the board
BUFIO6: R109.1; also elsewhere on the board
BUFIO7: R89.1; also elsewhere on the board
GND: C53.1, C54.2, C55.1, C56.2, C57.1, C58.2, C59.1, C60.2, C61.1, C62.2, C63.1, C64.2, C65.1, C66.2, R85.1, R86.2, R87.2, R90.1, R91.2, R92.2, R95.1, R96.2, R97.2, R100.1, R101.2, R102.2, R105.1, R106.2, R107.2, R110.1, R111.2, R112.2, R115.1, R116.2, R117.2, U18.2 (GND), U19.2 (GND), U20.2 (GND), U21.2 (GND), U22.2 (GND), U23.2 (GND), U24.2 (GND); also elsewhere on the board
unnamed: R84.2, R85.2, U18.3 (A)
unnamed: R87.1, R88.1, U18.4 (B)
unnamed: R89.2, R90.2, U19.3 (A)
unnamed: R92.1, R93.1, U19.4 (B)
unnamed: R94.2, R95.2, U20.3 (A)
unnamed: R97.1, R98.1, U20.4 (B)
unnamed: R99.2, R100.2, U21.3 (A)
unnamed: R102.1, R103.1, U21.4 (B)
unnamed: R104.2, R105.2, U22.3 (A)
unnamed: R107.1, R108.1, U22.4 (B)
unnamed: R109.2, R110.2, U23.3 (A)
unnamed: R112.1, R113.1, U23.4 (B)
unnamed: R114.2, R115.2, U24.3 (A)
unnamed: R117.1, R118.1, U24.4 (B)
VREF_VOUT: C54.1, C56.1, C58.1, C60.1, C62.1, C64.1, C66.1, U18.6 (VCCB), U19.6 (VCCB), U20.6 (VCCB), U21.6 (VCCB), U22.6 (VCCB), U23.6 (VCCB), U24.6 (VCCB); also elsewhere on the board

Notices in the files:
README.md:
License: MIT
